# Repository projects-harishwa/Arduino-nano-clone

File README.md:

Contains:
1. Circuit file
2. PCB 3d model and its related files
[ 10 layer PCB ]

[NOT TO BE SHARED WITHOUT PROPER CONSENT]

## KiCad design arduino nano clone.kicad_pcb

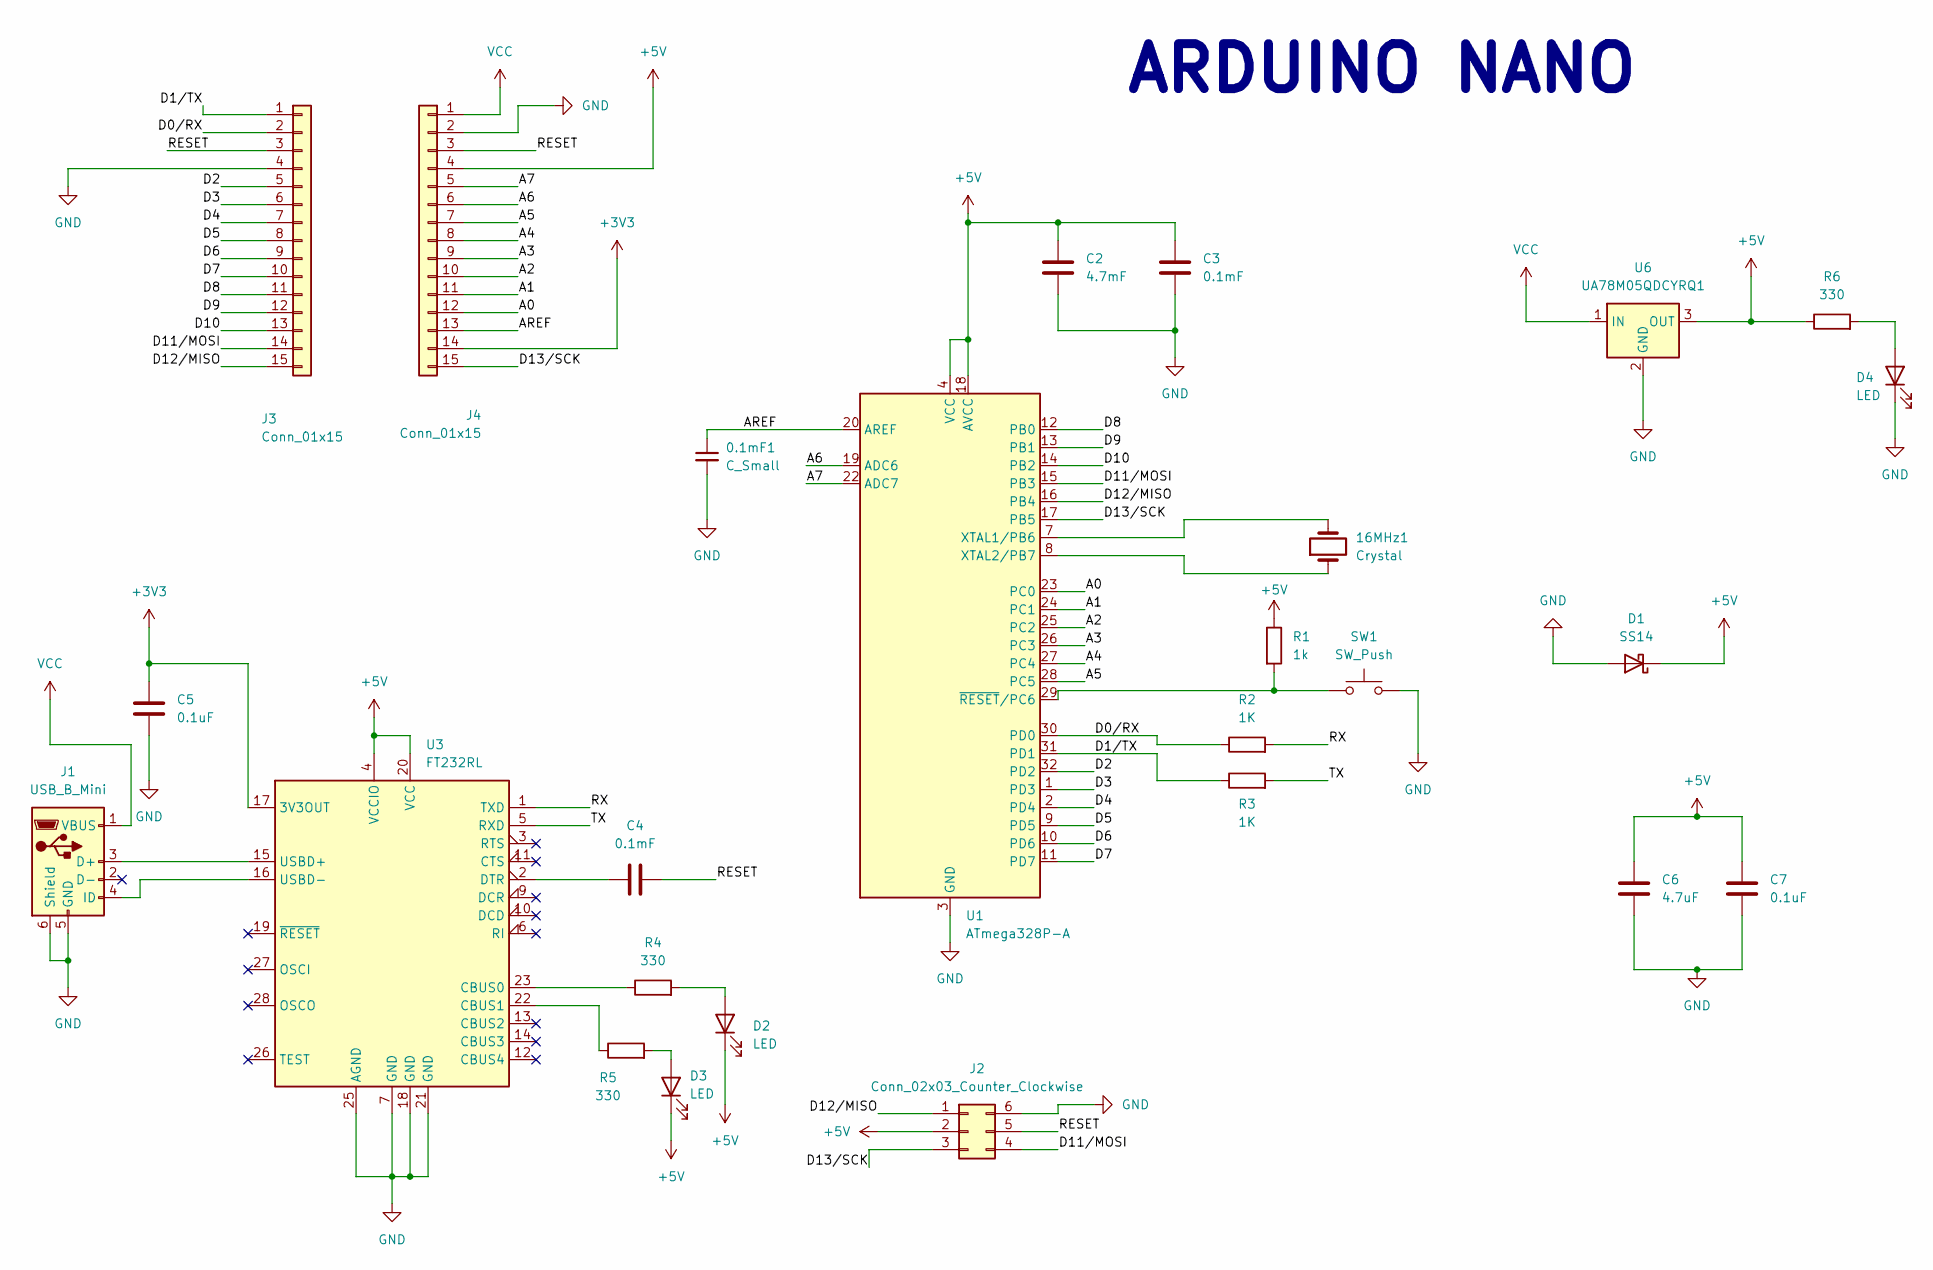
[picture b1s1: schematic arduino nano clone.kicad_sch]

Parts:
0.1mF1: C_Small; C_0603_1608Metric
16MHz1: Crystal; C_0603_1608Metric
C2: 4.7mF; C_1206_3216Metric
C3, C4: 0.1mF; C_0603_1608Metric
C5, C7: 0.1uF; C_0603_1608Metric
C6: 4.7uF; C_1206_3216Metric
D1: SS14; D_SMA
D2, D3, D4: LED; LED_0805_2012Metric
J1: USB_B_Mini; USB_Mini-B_AdamTech_MUSB-B5-S-VT-TSMT-1_SMD_Vertical
J2: Conn_02x03_Counter_Clockwise; PinHeader_2x03_P2.54mm_Vertical
J3, J4: Conn_01x15; PinHeader_1x15_P2.54mm_Vertical
R1: 1k; R_0603_1608Metric
R2, R3: 1K; R_0603_1608Metric
R4, R5, R6: 330; R_0603_1608Metric
SW1: SW_Push; SW_PUSH_6mm
U1: ATmega328P-A; TQFP-32_7x7mm_P0.8mm
U3: FT232RL; SSOP-28_5.3x10.2mm_P0.65mm
U6: UA78M05QDCYRQ1; SOT-223-3_TabPin2

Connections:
+3V3: C5.1, J4.14, U3.17 (3V3OUT)
+5V: C2.2, C3.1, C6.1, C7.1, D1.1 (K), D2.1 (K), D3.1 (K), J2.2, J4.4, R1.1, R6.1, U1.4 (VCC), U1.6 (VCC), U1.18 (AVCC), U3.4 (VCCIO), U3.20 (VCC), U6.3 (OUT)
/A0: J4.12, U1.23 (PC0)
/A1: J4.11, U1.24 (PC1)
/A2: J4.10, U1.25 (PC2)
/A3: J4.9, U1.26 (PC3)
/A4: J4.8, U1.27 (PC4)
/A5: J4.7, U1.28 (PC5)
/A6: J4.6, U1.19 (ADC6)
/A7: J4.5, U1.22 (ADC7)
/AREF: 0.1mF1.1, J4.13, U1.20 (AREF)
/D0/RX: J3.2, R2.1, U1.30 (PD0)
/D1/TX: J3.1, R3.1, U1.31 (PD1)
/D2: J3.5, U1.32 (PD2)
/D3: J3.6, U1.1 (PD3)
/D4: J3.7, U1.2 (PD4)
/D5: J3.8, U1.9 (PD5)
/D6: J3.9, U1.10 (PD6)
/D7: J3.10, U1.11 (PD7)
/D8: J3.11, U1.12 (PB0)
/D9: J3.12, U1.13 (PB1)
/D10: J3.13, U1.14 (PB2)
/D11/MOSI: J2.4, J3.14, U1.15 (PB3)
/D12/MISO: J2.1, J3.15, U1.16 (PB4)
/D13/SCK: J2.3, J4.15, U1.17 (PB5)
/RESET: C4.2, J2.5, J3.3, J4.3
/RX: R2.2, U3.1 (TXD)
/TX: R3.2, U3.5 (RXD)
GND: 0.1mF1.2, C2.1, C3.2, C5.2, C6.2, C7.2, D1.2 (A), D4.1 (K), J1.5 (GND), J1.6 (Shield), J2.6, J3.4, J4.2, SW1.2, U1.3 (GND), U1.5 (GND), U1.21 (GND), U3.7 (GND), U3.18 (GND), U3.21 (GND), U3.25 (AGND), U6.2 (GND)
unnamed: D2.2 (A), R4.2
unnamed: D3.2 (A), R5.2
unnamed: D4.2 (A), R6.2
unnamed: J1.3 (D+), U3.15 (USBD+)
unnamed: J1.4 (ID), U3.16 (USBD-)
unnamed: 16MHz1.2, U1.7 (XTAL1/PB6)
unnamed: 16MHz1.1, U1.8 (XTAL2/PB7)
unnamed: R1.2, SW1.1, U1.29 (~RESET/PC6)
unnamed: R4.1, U3.23 (CBUS0)
unnamed: R5.1, U3.22 (CBUS1)
unnamed: C4.1, U3.2 (DTR)
VCC: J1.1 (VBUS), J4.1, U6.1 (IN)

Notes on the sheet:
ARDUINO NANO

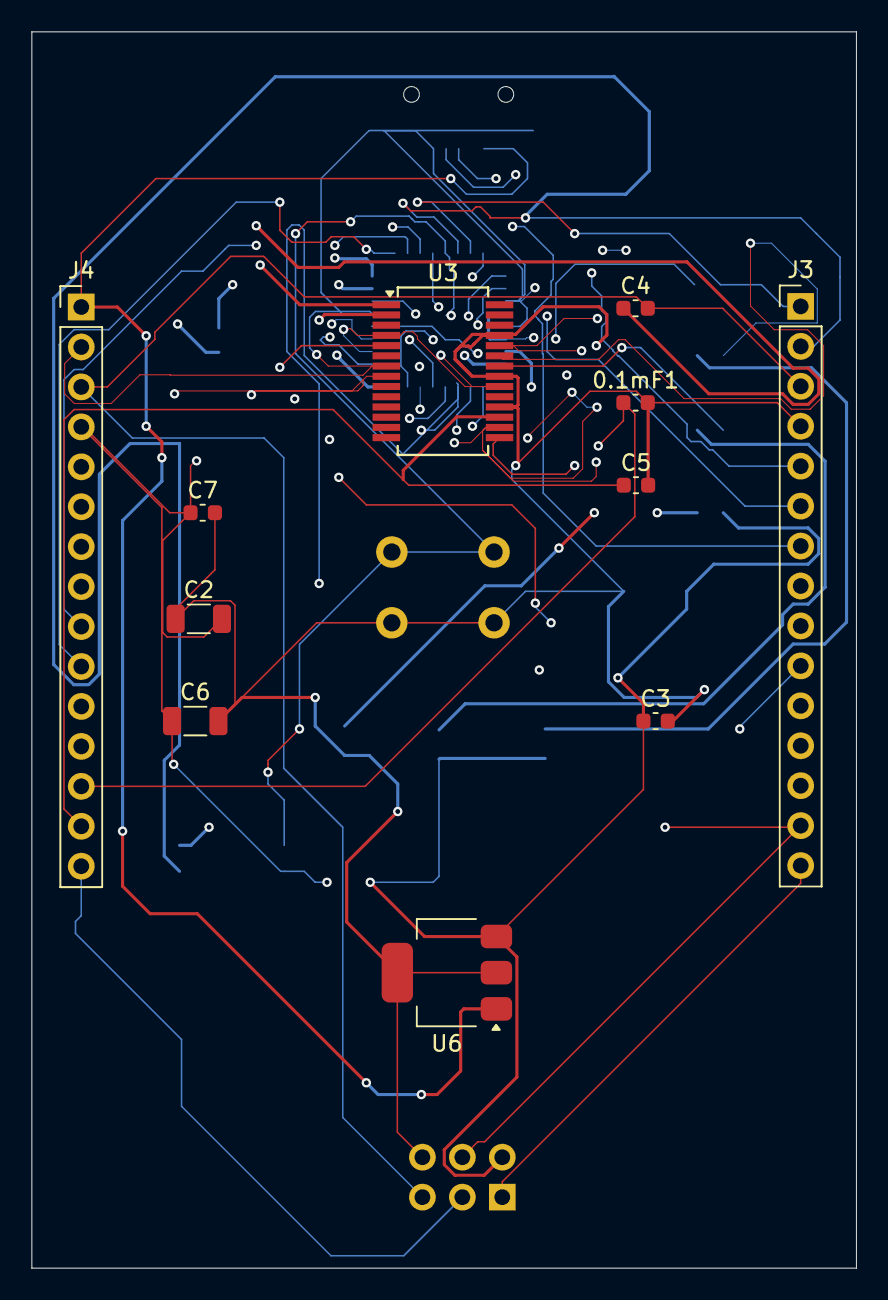
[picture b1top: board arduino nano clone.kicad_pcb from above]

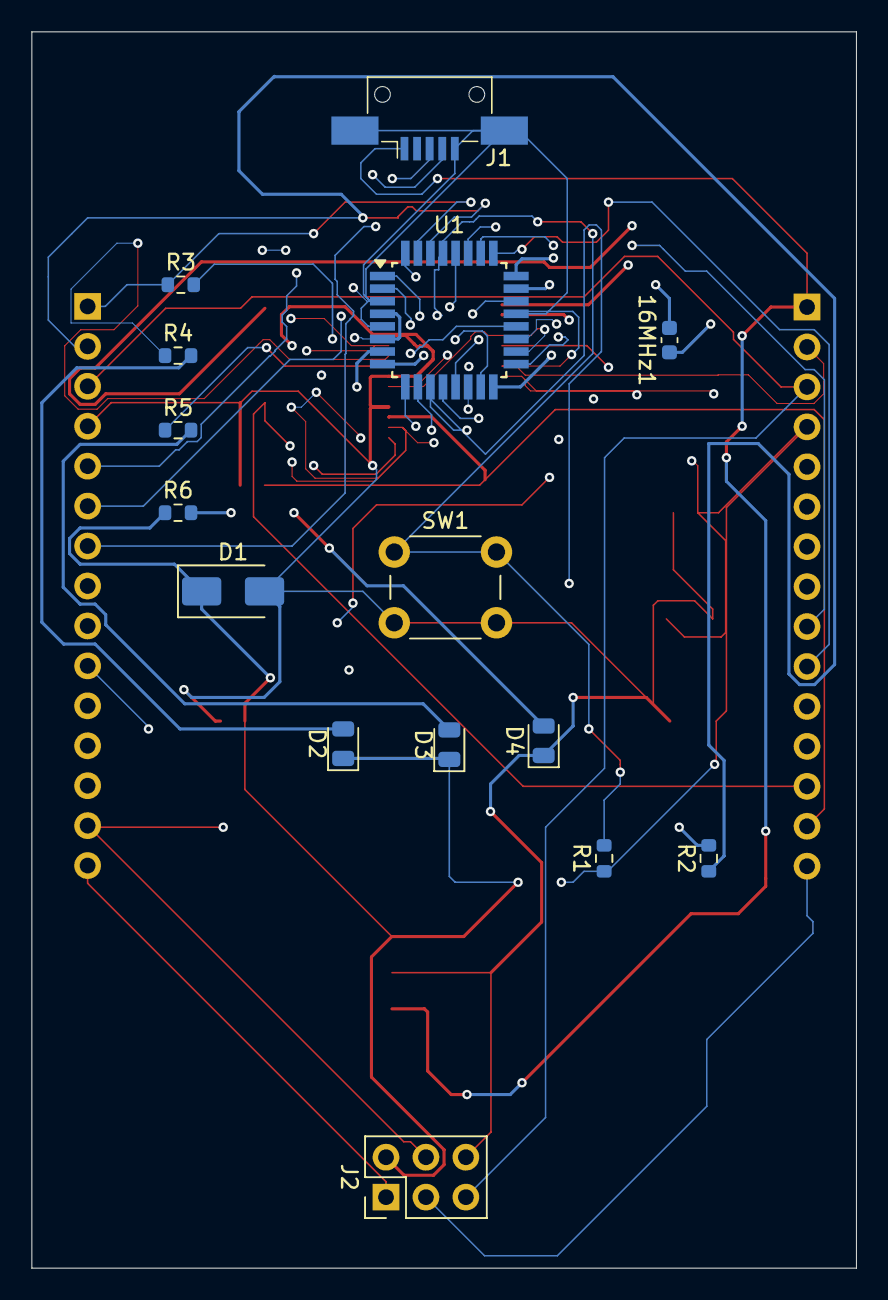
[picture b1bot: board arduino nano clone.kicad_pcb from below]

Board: 10 copper layers, 52.4 x 78.6 mm, 26 parts (15 on the bottom side), 41 nets.

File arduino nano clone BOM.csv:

"Reference","Qty","Value","DNP","Exclude from BOM","Exclude from Board","Footprint","Datasheet"
"0.1mF1","1","C_Small","","","","Capacitor_SMD:C_0603_1608Metric","~"
"16MHz1","1","Crystal","","","","Capacitor_SMD:C_0603_1608Metric","~"
"C2","1","4.7mF","","","","Capacitor_SMD:C_1206_3216Metric","~"
"C3,C4","2","0.1mF","","","","Capacitor_SMD:C_0603_1608Metric","~"
"C5,C7","2","0.1uF","","","","Capacitor_SMD:C_0603_1608Metric","~"
"C6","1","4.7uF","","","","Capacitor_SMD:C_1206_3216Metric","~"
"D1","1","SS14","","","","Diode_SMD:D_SMA","https://www.vishay.com/docs/88746/ss12.pdf"
"D2,D3,D4","3","LED","","","","LED_SMD:LED_0805_2012Metric","~"
"J1","1","USB_B_Mini","","","","Connector_USB:USB_Mini-B_AdamTech_MUSB-B5-S-VT-TSMT-1_SMD_Vertical","~"
"J2","1","Conn_02x03_Counter_Clockwise","","","","Connector_PinHeader_2.54mm:PinHeader_2x03_P2.54mm_Vertical","~"
"J3,J4","2","Conn_01x15","","","","Connector_PinHeader_2.54mm:PinHeader_1x15_P2.54mm_Vertical","~"
"R1","1","1k","","","","Resistor_SMD:R_0603_1608Metric","~"
"R2,R3","2","1K","","","","Resistor_SMD:R_0603_1608Metric","~"
"R4,R5,R6","3","330","","","","Resistor_SMD:R_0603_1608Metric","~"
"SW1","1","SW_Push","","","","Button_Switch_THT:SW_PUSH_6mm","~"
"U1","1","ATmega328P-A","","","","Package_QFP:TQFP-32_7x7mm_P0.8mm","http://ww1.microchip.com/downloads/en/DeviceDoc/ATmega328_P%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"
"U3","1","FT232RL","","","","Package_SO:SSOP-28_5.3x10.2mm_P0.65mm","https://www.ftdichip.com/Support/Documents/DataSheets/ICs/DS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"
"U6","1","UA78M05QDCYRQ1","","","","Package_TO_SOT_SMD:SOT-223-3_TabPin2","https://www.ti.com/lit/gpn/UA78M-Q1"

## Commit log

2025-04-16 Arduino-commit
2025-04-16 Read readme
